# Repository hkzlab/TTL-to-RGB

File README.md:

# MDA/CGA/EGA/HERCULES TTL-to-ANALOG Converter

## Introduction

This board converts CGA/EGA/MDA/Hercules TTL signals into analog RGB signals that can be fed into a compatible monitor.

Depending on jumper settings, it can automatically detect MDA/Hercules and Hi-res EGA modes (uses vsync polarity detection), can be forced into low-res 64 colors EGA and can perform the "brown-fix" for CGA.

The board uses a GAL20V8 PLD to implement the conversions, sync polarity detection, brown-fix, etc.

The PLD is sandwiched between two '244 buffers to protect it from shorts and allow the user to experiment with different logic families to better handle the input. It is recommended to use an 'LS244 as the output buffer, an LS or an HCT is fine for the input.

This board does NOT perform any frequency conversion. You will need a monitor capable of syncing to 15, 18 and 21Khz.

### Pics!

Example of an hi-res EGA game

Example of a low-res EGA game, with palette choosen between the 64 EGA colors (instead of the 16 CGA colors)

### Disclaimer

I take NO responsibility for what happens if you decide to build and use this card. Your computer might crash, catch fire or be destroyed in other nasty ways.
You're encourauged to take what you deem fit from this, and use it in your projects!

### Functionalities

✅ means I tested the functionality and it works, ❌ means I tested the functionality and found issues, ? means that the functionality has yet to be tested.

* [✅] CGA
* [✅] EGA, low-res
* [✅] EGA, low-res, 64 colors
* [✅] EGA, hi-res
* [✅] MDA
* [?] Hercules

## Bill of Materials

**TODO**

## Known Issues

### Rev 1.4

While this revision of the board is basically the same circuit of the previous revisions with some reorganization, the board has not been tested yet!

### Rev 1.2

* Optional power is connected to pin 15 of the HD15 connector, which is not ideal, as the best option would be pin 9. This will be fixed in a later revision (1.4)

### Rev 1.1

* Pin 13 of the GAL is tied to GND, and is currently used to switch between detection modes (CGA/MDA/HERCULES vs CGA/EGA). It can be fixed by a mod
* The board does not provide an option for power output on the HD15 connector. This can be fixed by a mod. Note that the mod will connect power to pin 15, which is not ideal (best would be pin 9), but connecting to the proper location requires desoldering the HD15 and cut more traces.
* With a 12v PSU the regulator gets hot. Use a PSU between 7 and 9v.

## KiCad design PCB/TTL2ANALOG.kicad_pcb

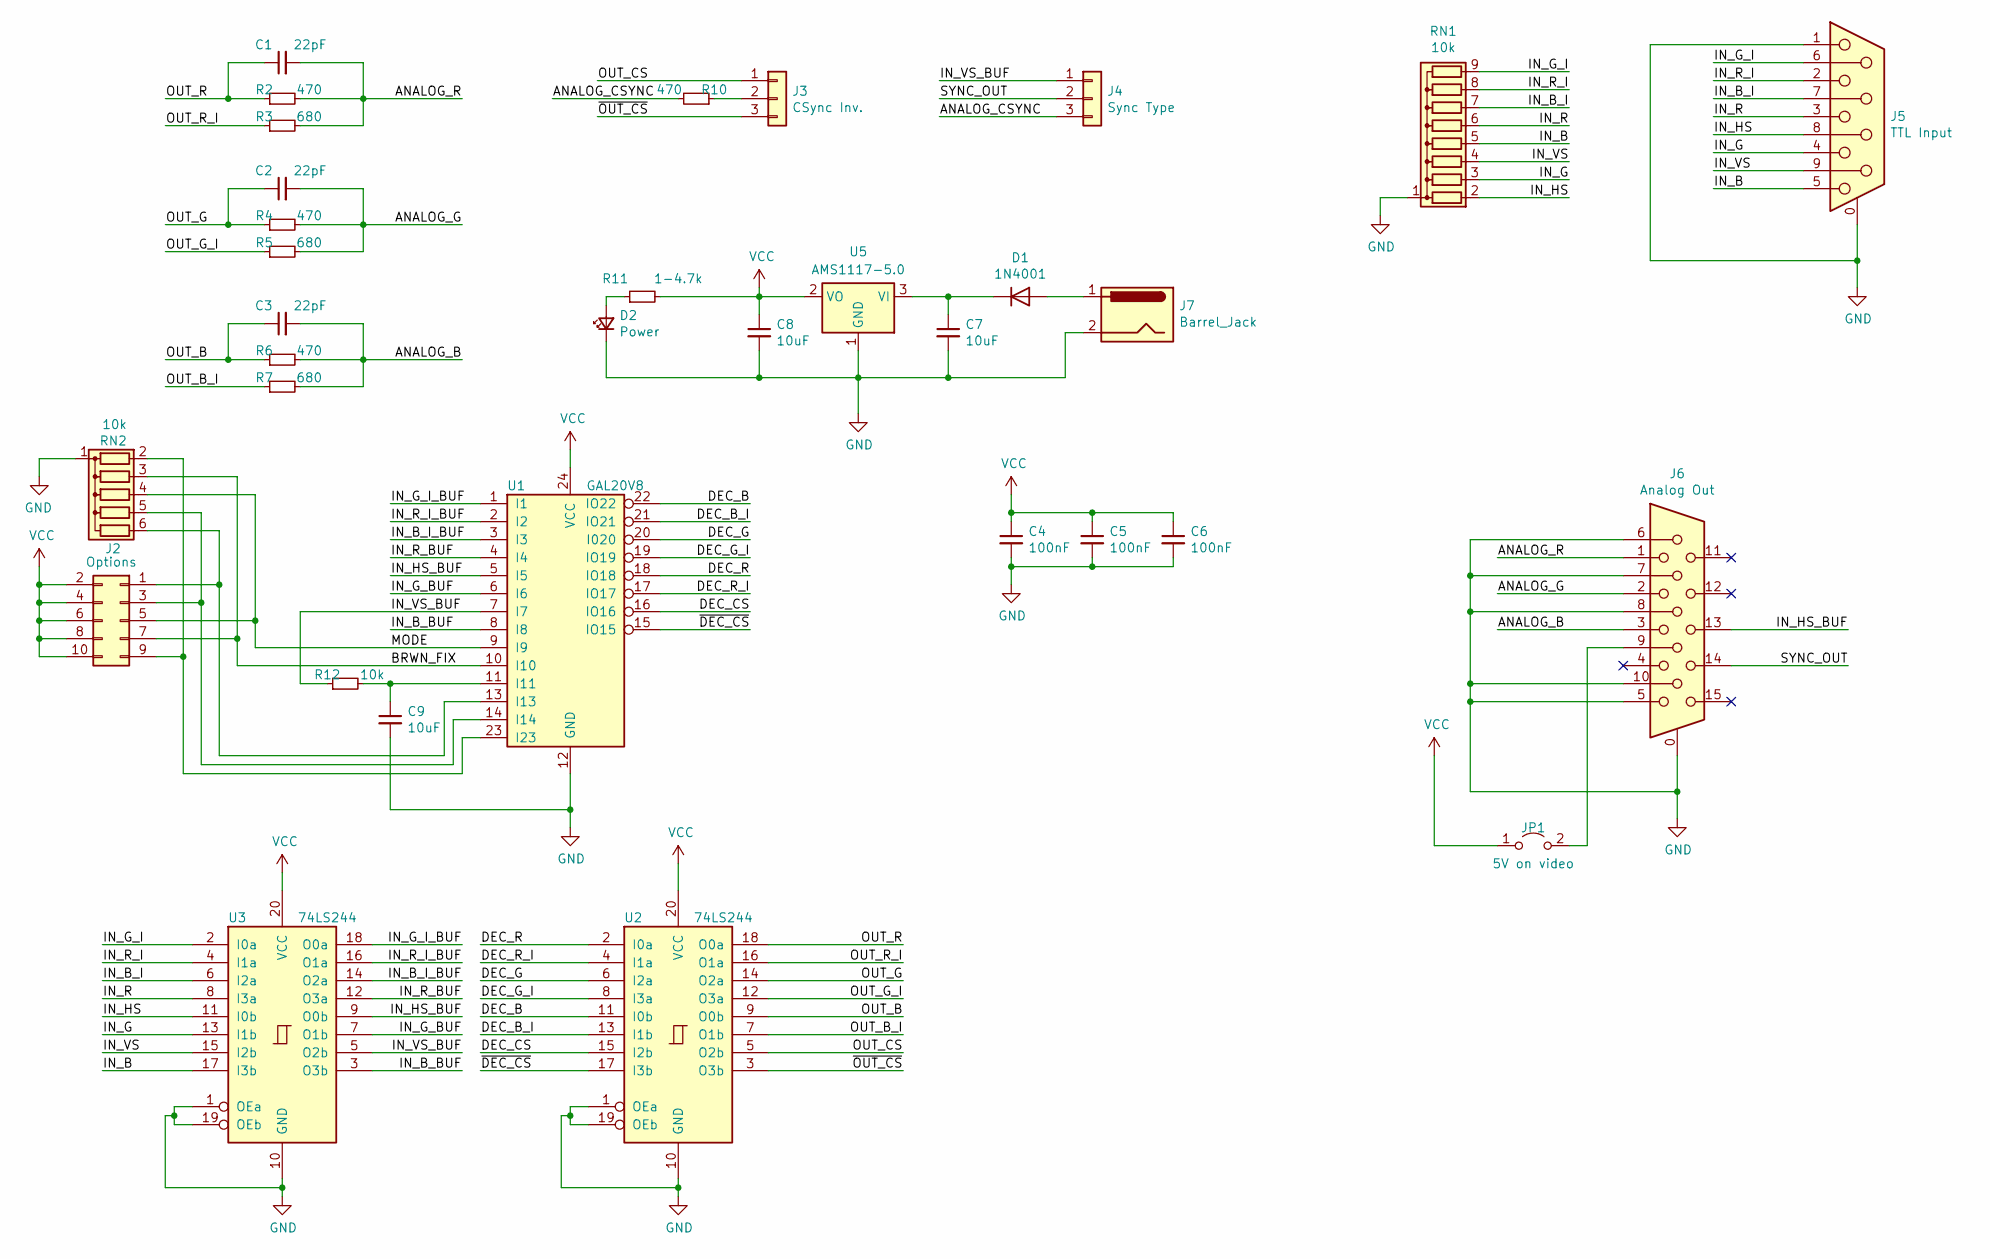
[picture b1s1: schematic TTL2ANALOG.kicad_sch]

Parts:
C1, C2, C3: 22pF; C_1206_3216Metric_Pad1.33x1.80mm_HandSolder
C4, C5, C6: 100nF; C_1206_3216Metric_Pad1.33x1.80mm_HandSolder
C7, C8, C9: 10uF; C_1206_3216Metric_Pad1.33x1.80mm_HandSolder
D1: 1N4001; D_DO-41_SOD81_P10.16mm_Horizontal
D2: Power; LED_1206_3216Metric_Pad1.42x1.75mm_HandSolder
J2: Options; PinHeader_2x05_P2.54mm_Vertical
J3: CSync Inv.; PinHeader_1x03_P2.54mm_Vertical
J4: Sync Type; PinHeader_1x03_P2.54mm_Vertical
J5: TTL Input; DSUB-9_Female_Horizontal_P2.77x2.84mm_EdgePinOffset4.94mm_H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
J6: Analog Out; DSUB-15-HD_Female_Horizontal_P2.29x1.98mm_EdgePinOffset3.03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
J7: Barrel_Jack; BarrelJack_Horizontal
JP1: 5V on video; PinHeader_1x02_P2.54mm_Vertical
R2, R4, R6, R10: 470; R_1206_3216Metric_Pad1.30x1.75mm_HandSolder
R3, R5, R7: 680; R_1206_3216Metric_Pad1.30x1.75mm_HandSolder
R11: 1-4.7k; R_1206_3216Metric_Pad1.30x1.75mm_HandSolder
R12: 10k; R_1206_3216Metric_Pad1.30x1.75mm_HandSolder
RN1: 10k; R_Array_SIP9
RN2: 10k; R_Array_SIP6
U1: GAL20V8; DIP-24_W7.62mm
U2, U3: 74LS244; DIP-20_W7.62mm_Socket
U5: AMS1117-5.0; SOT-223-3_TabPin2

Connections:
/ANALOG_B: C3.2, J6.3, R6.2, R7.2
/ANALOG_CSYNC: J4.3, R10.2
/ANALOG_G: C2.2, J6.2, R4.2, R5.2
/ANALOG_R: C1.2, J6.1, R2.2, R3.2
/BRWN_FIX: J2.7, RN2.3 (R2), U1.10 (I10)
/DEC_B: U1.22 (IO22), U2.11 (I0b)
/DEC_B_I: U1.21 (IO21), U2.13 (I1b)
/DEC_CS: U1.16 (IO16), U2.15 (I2b)
/DEC_G: U1.20 (I020), U2.6 (I2a)
/DEC_G_I: U1.19 (IO19), U2.8 (I3a)
/DEC_R: U1.18 (IO18), U2.2 (I0a)
/DEC_R_I: U1.17 (IO17), U2.4 (I1a)
/IN_B: J5.5, RN1.5 (R4), U3.17 (I3b)
/IN_B_BUF: U1.8 (I8), U3.3 (O3b)
/IN_B_I: J5.7, RN1.7 (R6), U3.6 (I2a)
/IN_B_I_BUF: U1.3 (I3), U3.14 (O2a)
/IN_G: J5.4, RN1.3 (R2), U3.13 (I1b)
/IN_G_BUF: U1.6 (I6), U3.7 (O1b)
/IN_G_I: J5.6, RN1.9 (R8), U3.2 (I0a)
/IN_G_I_BUF: U1.1 (I1), U3.18 (O0a)
/IN_HS: J5.8, RN1.2 (R1), U3.11 (I0b)
/IN_HS_BUF: J6.13, U1.5 (I5), U3.9 (O0b)
/IN_R: J5.3, RN1.6 (R5), U3.8 (I3a)
/IN_R_BUF: U1.4 (I4), U3.12 (O3a)
/IN_R_I: J5.2, RN1.8 (R7), U3.4 (I1a)
/IN_R_I_BUF: U1.2 (I2), U3.16 (O1a)
/IN_VS: J5.9, RN1.4 (R3), U3.15 (I2b)
/IN_VS_BUF: J4.1, R12.1, U1.7 (I7), U3.5 (O2b)
/MODE: J2.5, RN2.4 (R3), U1.9 (I9)
/OUT_B: C3.1, R6.1, U2.9 (O0b)
/OUT_B_I: R7.1, U2.7 (O1b)
/OUT_CS: J3.1, U2.5 (O2b)
/OUT_G: C2.1, R4.1, U2.14 (O2a)
/OUT_G_I: R5.1, U2.12 (O3a)
/OUT_R: C1.1, R2.1, U2.18 (O0a)
/OUT_R_I: R3.1, U2.16 (O1a)
/SYNC_OUT: J4.2, J6.14
/~DEC_CS: U1.15 (IO15), U2.17 (I3b)
/~OUT_CS: J3.3, U2.3 (O3b)
GND: C4.2, C5.2, C6.2, C7.2, C8.2, C9.2, D2.1 (K), J5.0 (PAD), J5.1, J6.0, J6.5, J6.6, J6.7, J6.8, J6.10, J7.2, RN1.1 (common), RN2.1 (common), U1.12 (GND), U2.1 (OEa), U2.10 (GND), U2.19 (OEb), U3.1 (OEa), U3.10 (GND), U3.19 (OEb), U5.1 (GND)
unnamed: D1.2 (A), J7.1
unnamed: C7.1, D1.1 (K), U5.3 (VI)
unnamed: D2.2 (A), R11.1
unnamed: J2.1, RN2.6 (R5), U1.13 (I13)
unnamed: J2.3, RN2.5 (R4), U1.14 (I14)
unnamed: J2.9, RN2.2 (R1), U1.23 (I23)
unnamed: J3.2, R10.1
unnamed: J6.9, JP1.2 (B)
unnamed: C9.1, R12.2, U1.11 (I11)
VCC: C4.1, C5.1, C6.1, C8.1, J2.2, J2.4, J2.6, J2.8, J2.10, JP1.1 (A), R11.2, U1.24 (VCC), U2.20 (VCC), U3.20 (VCC), U5.2 (VO)

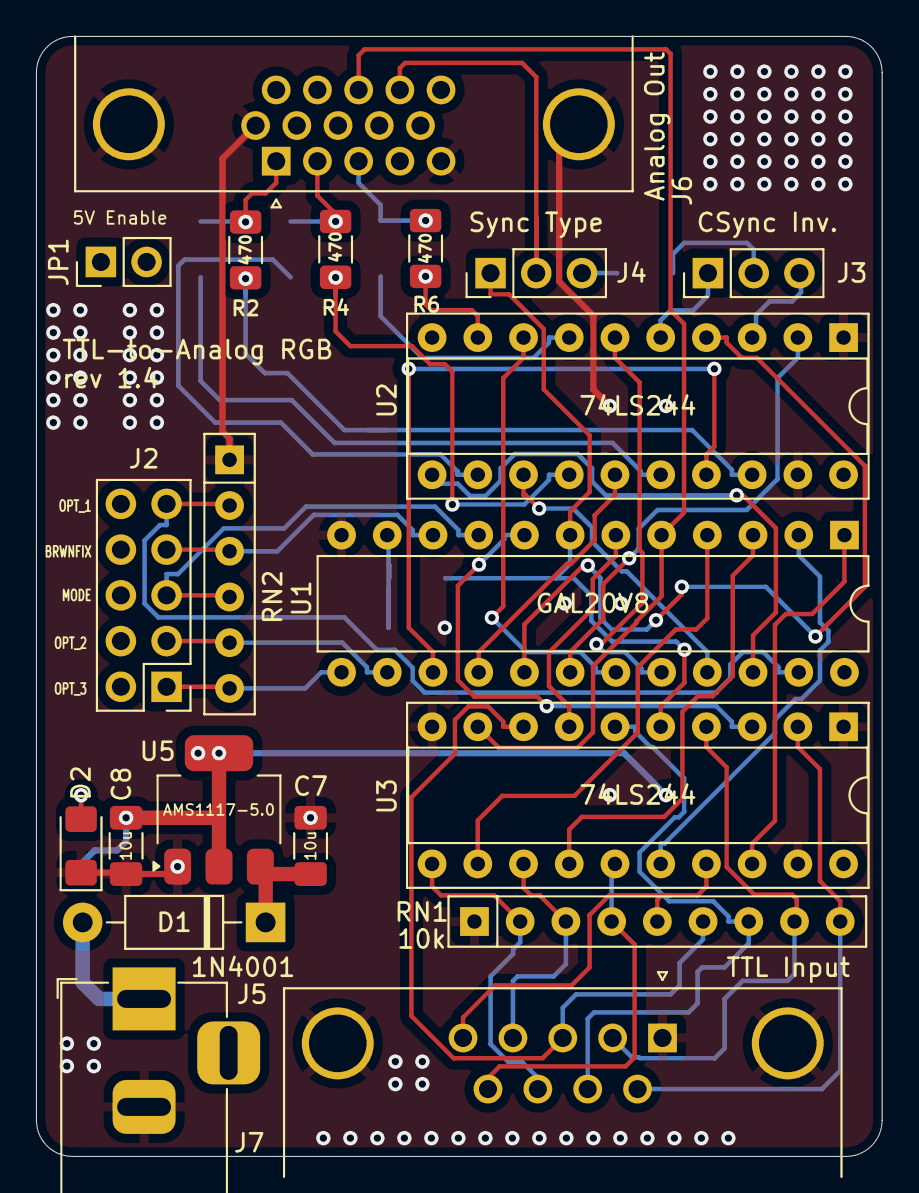
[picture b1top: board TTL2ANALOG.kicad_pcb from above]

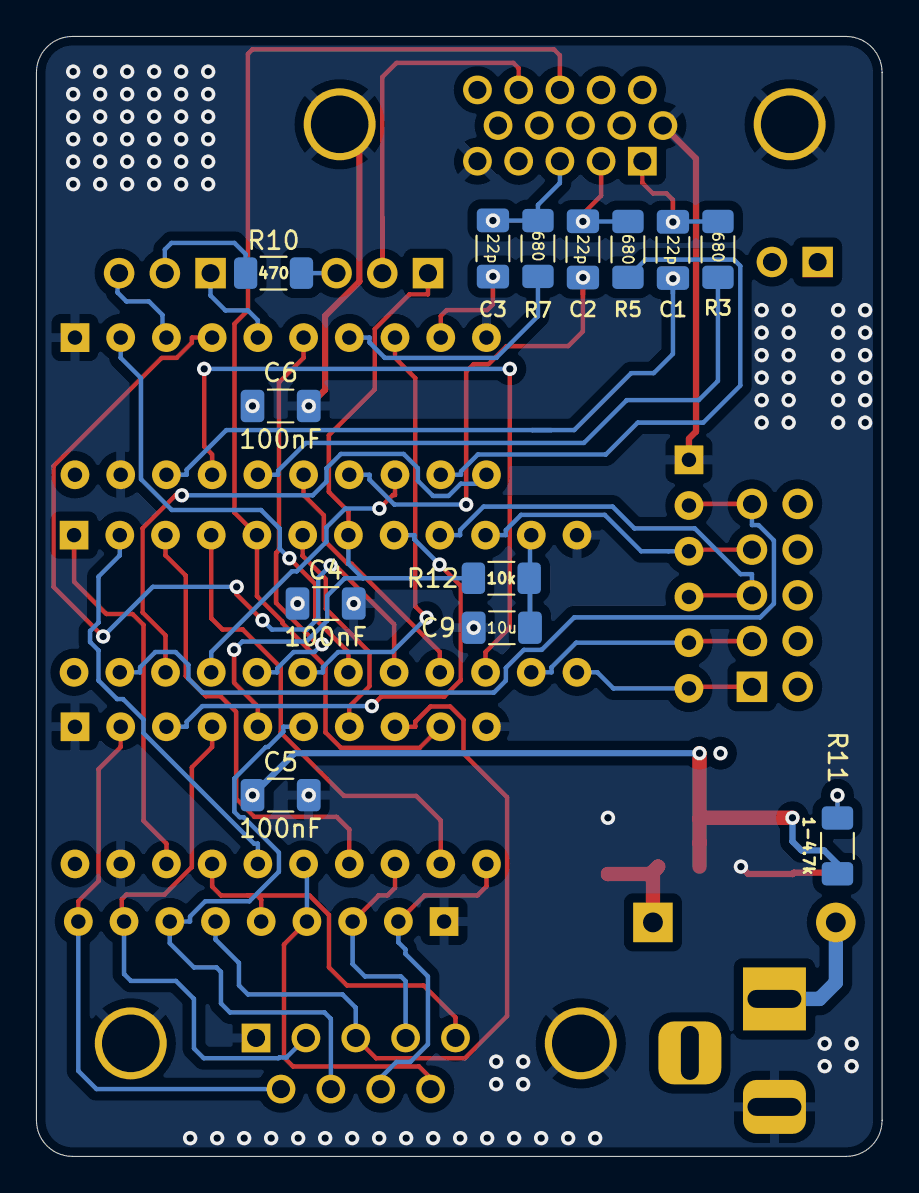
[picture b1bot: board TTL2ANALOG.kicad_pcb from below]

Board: 4 copper layers, 47.0 x 62.2 mm, 33 parts (13 on the bottom side), 50 nets.

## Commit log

2021-09-07 Begin adding new components to the board
2021-09-07 Begin drawing PCB
2021-09-07 Continue drawing PCB
2021-09-07 Draw PCB
2021-09-07 Complete main circuit
2021-09-07 Add PLD with test equations
2021-09-07 Notes to equations
2021-09-07 Add silkscreen
2021-09-07 Add gerbers
2021-09-07 Save prefs
2021-09-08 Update PLD equations
2021-09-08 Revert some changes for the PLD
2021-09-08 Add pulldown resistor on inputs
2021-09-09 Change PCB, use GAL20V8
2021-10-20 Update PCB to add 10k to VCC res to VGA out
2021-10-20 Use a TO220 7805 in new revision
2021-10-20 slightly change silkscreen
2021-10-20 Add gerbers for rev 1.2, remove deprecated and untested 1.1
2021-10-20 Restore 1.1, remove 1.0
2021-10-21 Begin drawing the 1.3 revision
2021-10-21 Changed the default state of the option plug
2021-10-21 Updated the PLD code to try autodetecting MDA/HERC
2021-10-27 Add new version of the PLD file
2021-10-28 Fix red intensity equation
2021-10-28 Replace a bridge with an header
2021-11-30 Add README and pics
2021-11-30 More pics
2021-11-30 Resized pic
2021-11-30 More notes
2023-10-23 Import to KiCad 7 and update the README with known issues
2024-10-19 Redraw version 1.4
2024-11-15 Update README, add schematic, and 1.4 picture
